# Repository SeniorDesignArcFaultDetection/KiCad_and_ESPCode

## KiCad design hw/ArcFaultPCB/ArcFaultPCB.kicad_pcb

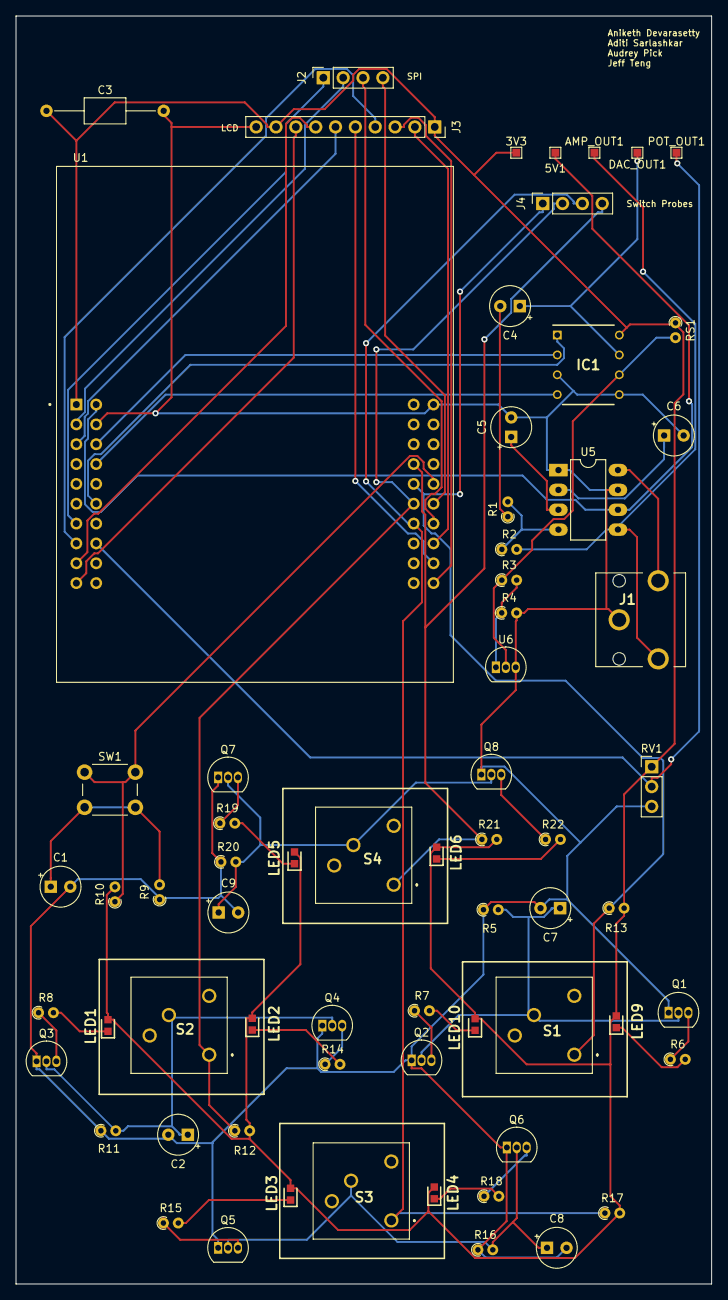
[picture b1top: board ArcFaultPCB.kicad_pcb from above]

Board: 2 copper layers, 89.0 x 162.3 mm, 67 parts (0 on the bottom side), 53 nets.

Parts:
3V3, 5V1: TestPoint; TestPoint_Pad_1.0x1.0mm
AMP_OUT1: TestPoint; TestPoint_Pad_1.0x1.0mm
C1, C2, C7, C8, C9: 1uF; CP_Radial_Tantal_D5.0mm_P2.50mm
C3: 10uF; C_Axial_L5.1mm_D3.1mm_P15.00mm_Horizontal
C4: .1 uF; CP_Radial_Tantal_D5.0mm_P2.50mm
C5: 1.0 uF; CP_Radial_Tantal_D5.0mm_P2.50mm
C6: 4.7 uF; CP_Radial_Tantal_D5.0mm_P2.50mm
DAC_OUT1: TestPoint; TestPoint_Pad_1.0x1.0mm
IC1: TLV5618AIP; ti_TLV5618AIP
J1: SJ1-3553NG; SJ13553NG
J2, J4: Conn_01x04_Socket; PinSocket_1x04_P2.54mm_Vertical
J3: Conn_01x10_Socket; PinSocket_1x10_P2.54mm_Vertical
LED1, LED2, LED3, LED4, LED5, LED6, LED9, LED10: 150060BS75000; LEDC1608X80N
POT_OUT1: TestPoint; TestPoint_Pad_1.0x1.0mm
Q1, Q2, Q3, Q4, Q5, Q6, Q7, Q8: 2N7000; TO-92_Inline
R1: 20k; R_Axial_DIN0204_L3.6mm_D1.6mm_P1.90mm_Vertical
R2, R9, R10: 10k; R_Axial_DIN0204_L3.6mm_D1.6mm_P1.90mm_Vertical
R3: 14k; R_Axial_DIN0204_L3.6mm_D1.6mm_P1.90mm_Vertical
R4: 3k; R_Axial_DIN0204_L3.6mm_D1.6mm_P1.90mm_Vertical
R5, R11, R16, R20: 8k; R_Axial_DIN0204_L3.6mm_D1.6mm_P1.90mm_Vertical
R6, R7, R8, R14, R15, R18, R19, R22: 330; R_Axial_DIN0204_L3.6mm_D1.6mm_P1.90mm_Vertical
R12, R13, R17, R21: 2k; R_Axial_DIN0204_L3.6mm_D1.6mm_P1.90mm_Vertical
RS1: 1.5k; R_Axial_DIN0204_L3.6mm_D1.6mm_P1.90mm_Vertical
RV1: R_Potentiometer; PinHeader_1x03_P2.54mm_Vertical
S1, S2, S3, S4: RIGHT; KS11R23CQD
SW1: SW_Reset; SW_PUSH_6mm
U1: EK-TM4C123GXL; ti_EKTM4C123GXL
U5: MCP34119P; DIP-8_W7.62mm_LongPads
U6: LM4041LP-ADJ; TO-92_Inline

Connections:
+3V3: 3V3.1, C3.1, IC1.8 (VDD), J3.1, J3.9, LED1.2 (A), LED2.2 (A), LED3.2 (A), LED4.2 (A), LED5.2 (A), LED6.2 (A), LED9.2 (A), LED10.2 (A), R10.2, R12.2, R13.2, R17.2, R21.2, RS1.1, RV1.1, U1.J1_1 (+3.3V)
+5V: 5V1.1, U1.J3_1 (+VBUS), U5.6 (Vcc)
/AMP_OUT: AMP_OUT1.1, J1.2 (TIP), R2.2, U5.5 (VO1)
/DAC_OUT: C4.1, DAC_OUT1.1, IC1.7 (OUTB)
/POT_OUT: POT_OUT1.1, RV1.2, U1.J3_8 (PE2)
/RST: R10.1, SW1.1, U1.J2_5 (~TARGETRST)
/SDC_CS: J3.6, U1.J1_3 (PB0)
/SS1_FS: IC1.4 (OUTA), U1.J3_4 (PD1)
/SS1_MOSI: IC1.1 (DIN), U1.J3_6 (PD3)
/SS1_SCK: IC1.2 (SCLK), U1.J3_3 (PD0)
/SS2_FS: J2.2, U1.J1_2 (PB5)
/SS2_MISO: J2.3, U1.J2_7 (PB6)
/SS2_MOSI: J2.4, U1.J2_6 (PB7)
/SS2_SCK: J2.1, U1.J1_7 (PB4)
/SW_DOWN: J4.3, R17.1, S3.1, U1.J4_7 (PC7)
/SW_LEFT: J4.2, R12.1, S2.1, U1.J4_6 (PC6)
/SW_RIGHT: J4.1, R13.1, S1.1, U1.J4_5 (PC5)
/SW_UP: J4.4, R21.1, S4.1, U1.J4_4 (PC4)
/TFT_CS: J3.5, U1.J2_9 (PA3)
/TFT_D/C: J3.7, U1.J1_9 (PA6)
/TFT_MISO: J3.2, U1.J2_8 (PA4)
/TFT_MOSI: J3.4, U1.J1_8 (PA5)
/TFT_RST: J3.8, U1.J1_10 (PA7)
/TFT_SCK: J3.3, U1.J2_10 (PA2)
/Vref: IC1.6 (REF), R3.1, RS1.2, U6.2 (K)
GND: C1.2, C2.2, C3.2, C5.2, C6.2, C7.2, C8.2, C9.2, IC1.3 (~CS), IC1.5 (AGND), J1.1 (SLEEVE), J3.10, Q1.1 (S), Q2.1 (S), Q3.1 (S), Q4.1 (S), Q5.1 (S), Q6.1 (S), Q7.1 (S), Q8.1 (S), R4.2, R5.1, R9.1, R11.1, R16.1, R20.1, RV1.3, U1.J2_1 (GND), U1.J3_2 (GND), U5.1 (CD), U5.7 (GND), U6.3 (A)
unnamed: C1.1, R9.2, SW1.2
unnamed: C4.2, R1.1
unnamed: J1.3 (RING), U5.8 (VO2)
unnamed: LED1.1 (K), R8.2
unnamed: LED2.1 (K), R14.2
unnamed: LED3.1 (K), R15.2
unnamed: LED4.1 (K), R18.2
unnamed: LED5.1 (K), R19.2
unnamed: LED6.1 (K), R22.2
unnamed: LED9.1 (K), R6.2
unnamed: LED10.1 (K), R7.2
unnamed: Q1.3 (D), R6.1
unnamed: C7.1, Q1.2 (G), Q2.2 (G), R5.2, S1.3
unnamed: Q2.3 (D), R7.1
unnamed: Q3.3 (D), R8.1
unnamed: C2.1, Q3.2 (G), Q4.2 (G), R11.2, S2.3
unnamed: Q4.3 (D), R14.1
unnamed: Q5.3 (D), R15.1
unnamed: C8.1, Q5.2 (G), Q6.2 (G), R16.2, S3.3
unnamed: Q6.3 (D), R18.1
unnamed: Q7.3 (D), R19.1
unnamed: C9.1, Q7.2 (G), Q8.2 (G), R20.2, S4.3
unnamed: Q8.3 (D), R22.1
unnamed: C5.1, U5.3 (FC1)
unnamed: C6.1, U5.2 (FC2)
unnamed: R1.2, R2.1, U5.4 (VIN)
unnamed: R3.2, R4.1, U6.1 (FB)

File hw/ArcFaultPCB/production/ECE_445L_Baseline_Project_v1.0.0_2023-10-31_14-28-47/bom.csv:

Designator,Footprint,Quantity,Value,LCSC Part #
"3V3, 5V1, AMP_OUT1, DAC_OUT1, POT_OUT1",TestPoint_Pad_1.0x1.0mm,5,TestPoint,
"C1, C2, C7, C8, C9",CP_Radial_Tantal_D5.0mm_P2.50mm,5,1uF,
C3,C_Axial_L5.1mm_D3.1mm_P15.00mm_Horizontal,1,10uF,
C4,CP_Radial_Tantal_D5.0mm_P2.50mm,1,.1 uF,
C5,CP_Radial_Tantal_D5.0mm_P2.50mm,1,1.0 uF,
C6,CP_Radial_Tantal_D5.0mm_P2.50mm,1,4.7 uF,
IC1,ti_TLV5618AIP,1,TLV5618AIP,
J1,SJ13553NG,1,SJ1-3553NG,
"J2, J4",PinSocket_1x04_P2.54mm_Vertical,2,Conn_01x04_Socket,
J3,PinSocket_1x10_P2.54mm_Vertical,1,Conn_01x10_Socket,
"LED1, LED10, LED2, LED3, LED4, LED5, LED6, LED9",LEDC1608X80N,8,150060BS75000,
"Q1, Q2, Q3, Q4, Q5, Q6, Q7, Q8",TO-92_Inline,8,2N7000,
R1,R_Axial_DIN0204_L3.6mm_D1.6mm_P1.90mm_Vertical,1,20k,
"R10, R2, R9",R_Axial_DIN0204_L3.6mm_D1.6mm_P1.90mm_Vertical,3,10k,
"R11, R16, R20, R5",R_Axial_DIN0204_L3.6mm_D1.6mm_P1.90mm_Vertical,4,8k,
"R12, R13, R17, R21",R_Axial_DIN0204_L3.6mm_D1.6mm_P1.90mm_Vertical,4,2k,
"R14, R15, R18, R19, R22, R6, R7, R8",R_Axial_DIN0204_L3.6mm_D1.6mm_P1.90mm_Vertical,8,330,
R3,R_Axial_DIN0204_L3.6mm_D1.6mm_P1.90mm_Vertical,1,14k,
R4,R_Axial_DIN0204_L3.6mm_D1.6mm_P1.90mm_Vertical,1,3k,
RS1,R_Axial_DIN0204_L3.6mm_D1.6mm_P1.90mm_Vertical,1,1.5k,
RV1,PinHeader_1x03_P2.54mm_Vertical,1,R_Potentiometer,
"S1, S2, S3, S4",KS11R23CQD,4,RIGHT,
SW1,SW_PUSH_6mm,1,SW_Reset,
U1,ti_EKTM4C123GXL,1,EK-TM4C123GXL,
U5,DIP-8_W7.62mm_LongPads,1,MCP34119P,
U6,TO-92_Inline,1,LM4041LP-ADJ,

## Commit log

2023-12-12 input esp code & kicad setup
2023-12-12 KiCad with all right embedded components
2023-12-12 KiCad PCB ready for more components and PCB layout
2023-12-12 arc fault detection schematic mock up
2023-12-17 Add files via upload
    This is the PCB schematic for the flyback converter. All components are included except for the MOSFET model and gate signal for MOFSET. The inputs are intended for banana cables.
2024-02-04 Basic transmission and receiving code
    This code is not optimized for latency/ speed yet, but the receiver connects to the internet and hosts a server. Desired functionality works
2024-03-26 Modified sender and receiver files for latency
    These files have reduced time delays for sending and receiving data in order for us to see how quickly data can be sent and received. They also have serial output code commented out to optimize perfo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
2024-04-19 Final code modified to take comparator input
    Has acknowledgements at top of each file for source of code
